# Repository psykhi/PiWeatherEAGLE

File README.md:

PiWeatherEAGLE
==============

This repository contains EAGLE boards/schematics/gerber files for the PiWeather weather station project.
To learn more, see http://theboredengineers.com.

main_indoor_sensor is an indoor board that can monitor temperature, humidity and pressure.
It is described here : http://theboredengineers.com/2014/05/piweather-part-4-first-pcbs/

rpi_shield is Raspberry Pi shield hosting a nRF24L01+ RF transimtter. 

If you are interested in this project, please visit http://theboredengineers.com, let a comment
or send an email to alex@theboredengineers.com

:)

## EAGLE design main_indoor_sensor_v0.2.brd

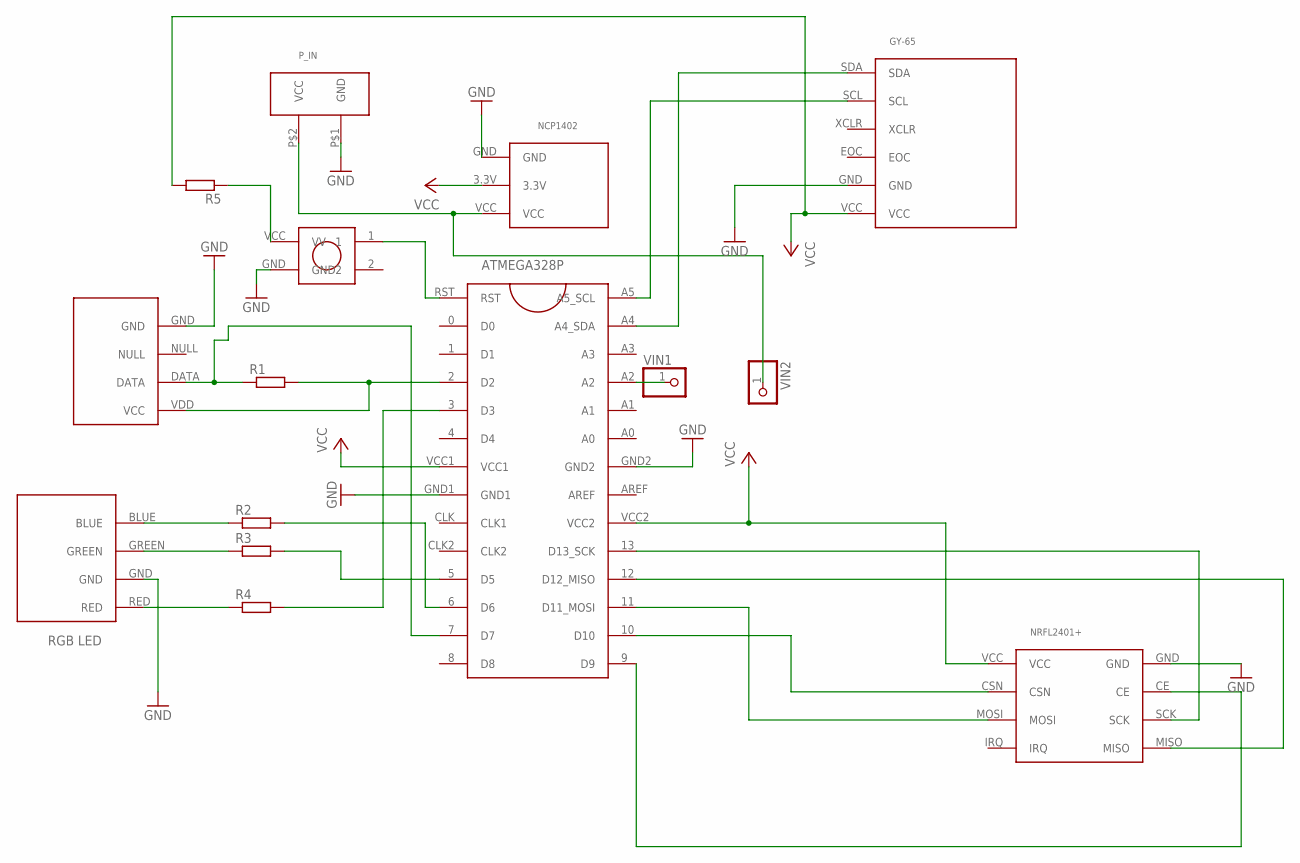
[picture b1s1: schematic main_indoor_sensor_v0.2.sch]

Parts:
GY-65: GY-65; GY_65
NCP1402: NCP1402SPARKFUN; NCP1402
NRFL2401+: NRFL24L01_8P; NRF24L01_10P
P_IN: 2PINCONNECTORSIMPLE; 2PINCONNECTOR
R1, R2, R3, R4, R5: R0204/7; 0204/7
U$1: ATMEGA328PARDUINO; ATMEGA328P
U$2: KRS_0612_OK; KRS0612_RIGHT
U$3: DHT22WHITE; DHT22
U$6: RGB_LED5MM; RGB_LED
VIN1, VIN2: PINHD-1X1; 1X01

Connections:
GND: GY-65.GND, NCP1402.GND, NRFL2401+.GND, P_IN.P$1 (GND), U$1.GND1, U$1.GND2, U$2.GND, U$3.GND, U$6.GND
unnamed: GY-65.SDA, U$1.A4 (A4_SDA)
unnamed: GY-65.SCL, U$1.A5 (A5_SCL)
unnamed: NRFL2401+.SCK, U$1.13 (D13_SCK)
unnamed: NRFL2401+.MISO, U$1.12 (D12_MISO)
unnamed: NRFL2401+.MOSI, U$1.11 (D11_MOSI)
unnamed: R1.2, U$1.2 (D2), U$3.VDD (VCC)
unnamed: R1.1, U$1.7 (D7), U$3.DATA
unnamed: R4.2, U$1.3 (D3)
unnamed: R2.1, U$6.BLUE
unnamed: R3.1, U$6.GREEN
unnamed: R2.2, U$1.6 (D6)
unnamed: R3.2, U$1.5 (D5)
unnamed: R4.1, U$6.RED
unnamed: NRFL2401+.CSN, U$1.10 (D10)
unnamed: NRFL2401+.CE, U$1.9 (D9)
unnamed: U$1.RST, U$2.1
unnamed: NCP1402.VCC, P_IN.P$2 (VCC), VIN2.1
unnamed: R5.1, U$2.VCC (VV)
unnamed: U$1.A2, VIN1.1
VCC: GY-65.VCC, NCP1402.3.3V, NRFL2401+.VCC, R5.2, U$1.VCC1, U$1.VCC2

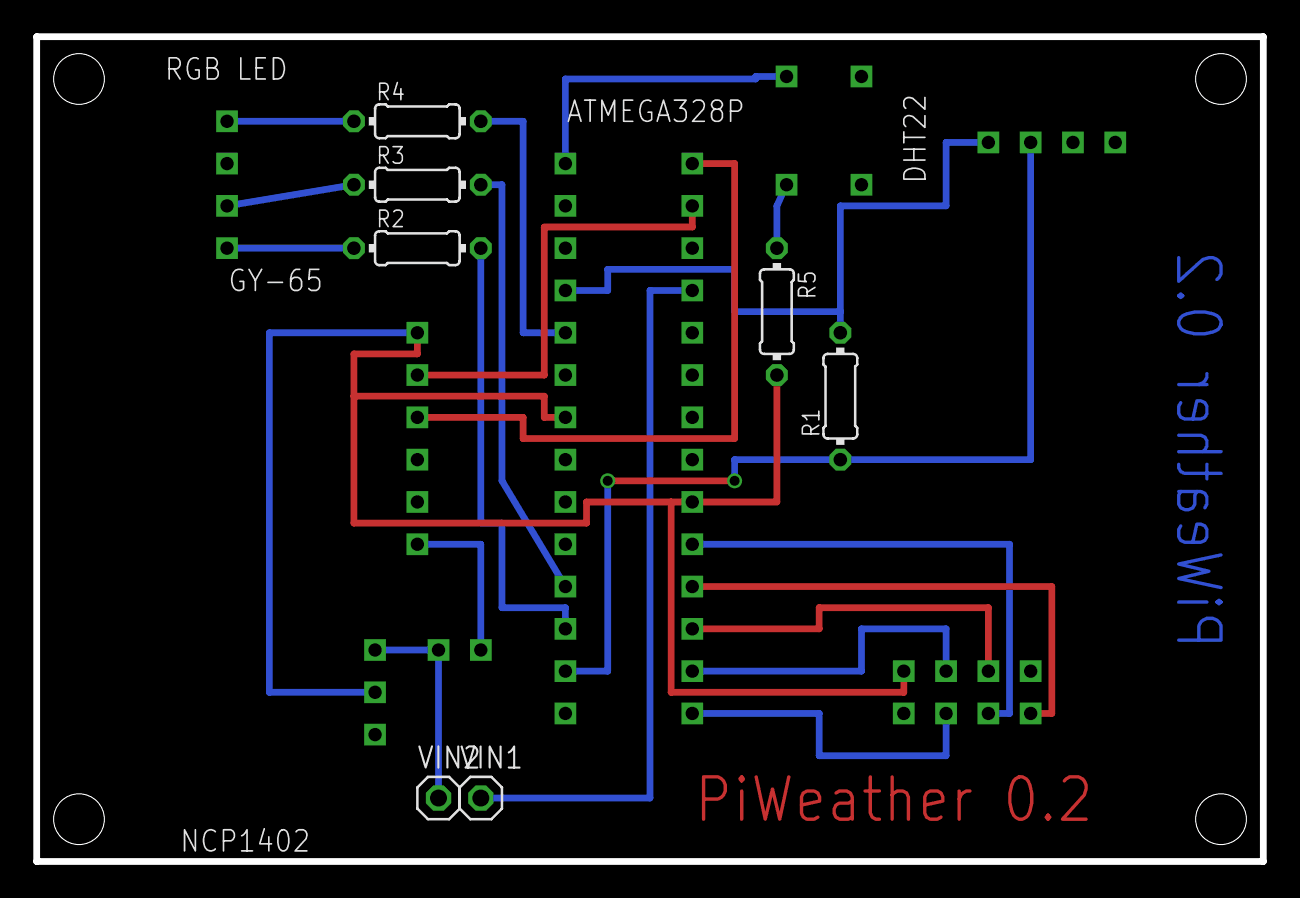
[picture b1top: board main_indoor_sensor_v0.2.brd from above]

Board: 2 copper layers, 73.7 x 49.5 mm, 15 parts (0 on the bottom side), 21 nets.

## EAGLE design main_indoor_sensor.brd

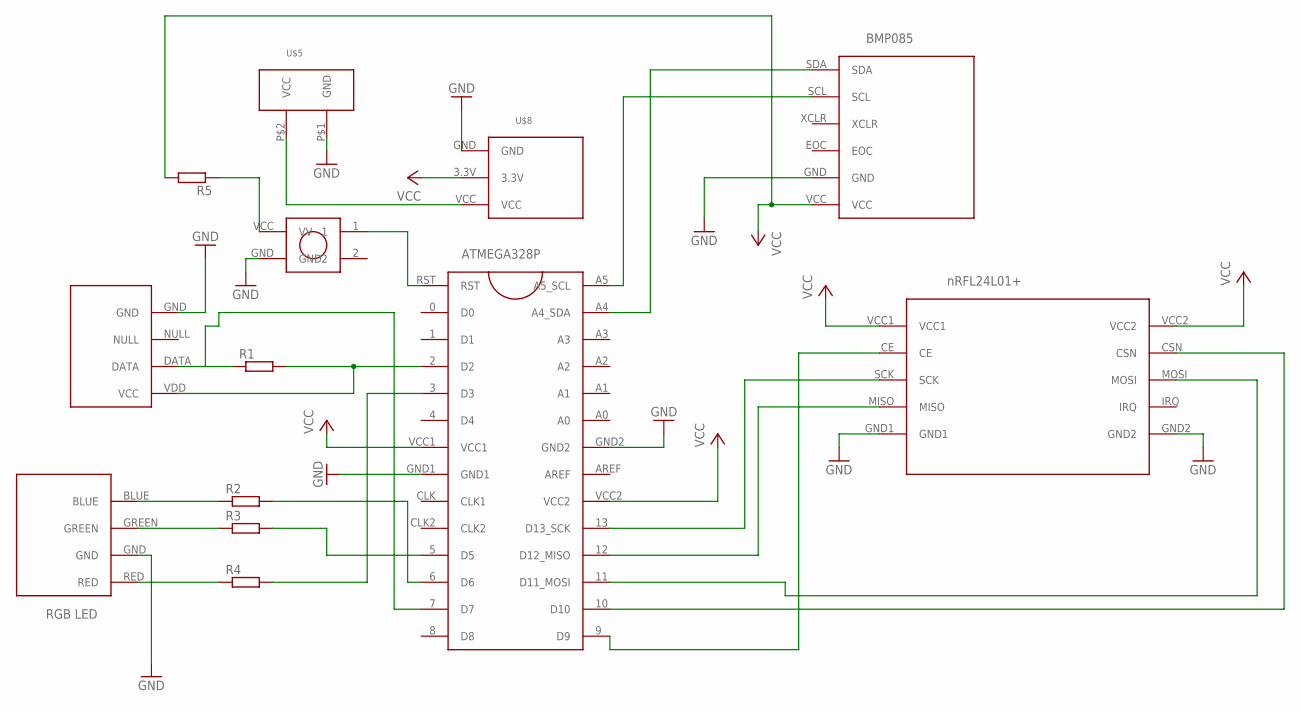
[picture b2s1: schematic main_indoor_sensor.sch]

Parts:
R1, R2, R3, R4, R5: R0204/7; 0204/7
U$1: ATMEGA328PARDUINO; ATMEGA328P
U$2: BMP085SPARKFUN; BMP085
U$3: DHT22WHITE; DHT22
U$4: NRF24L0110PINS; NRF24L01
U$5: 2PINCONNECTORSIMPLE; 2PINCONNECTOR
U$6: RGB_LED5MM; RGB_LED
U$7: KRS0612PUSH; KRS0612
U$8: NCP1402SPARKFUN; NCP1402

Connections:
GND: U$1.GND1, U$1.GND2, U$2.GND, U$3.GND, U$4.GND1, U$4.GND2, U$5.P$1 (GND), U$6.GND, U$7.GND, U$8.GND
unnamed: U$1.A4 (A4_SDA), U$2.SDA
unnamed: U$1.A5 (A5_SCL), U$2.SCL
unnamed: U$1.13 (D13_SCK), U$4.SCK
unnamed: U$1.12 (D12_MISO), U$4.MISO
unnamed: U$1.11 (D11_MOSI), U$4.MOSI
unnamed: R1.2, U$1.2 (D2), U$3.VDD (VCC)
unnamed: R1.1, U$1.7 (D7), U$3.DATA
unnamed: R4.2, U$1.3 (D3)
unnamed: R2.1, U$6.BLUE
unnamed: R3.1, U$6.GREEN
unnamed: R2.2, U$1.6 (D6)
unnamed: R3.2, U$1.5 (D5)
unnamed: R4.1, U$6.RED
unnamed: U$1.10 (D10), U$4.CSN
unnamed: U$1.9 (D9), U$4.CE
unnamed: U$1.RST, U$7.1
unnamed: U$5.P$2 (VCC), U$8.VCC
unnamed: R5.1, U$7.VCC (VV)
RASTNEST: R5.2, U$1.VCC1, U$1.VCC2, U$2.VCC, U$4.VCC1, U$4.VCC2, U$8.3.3V

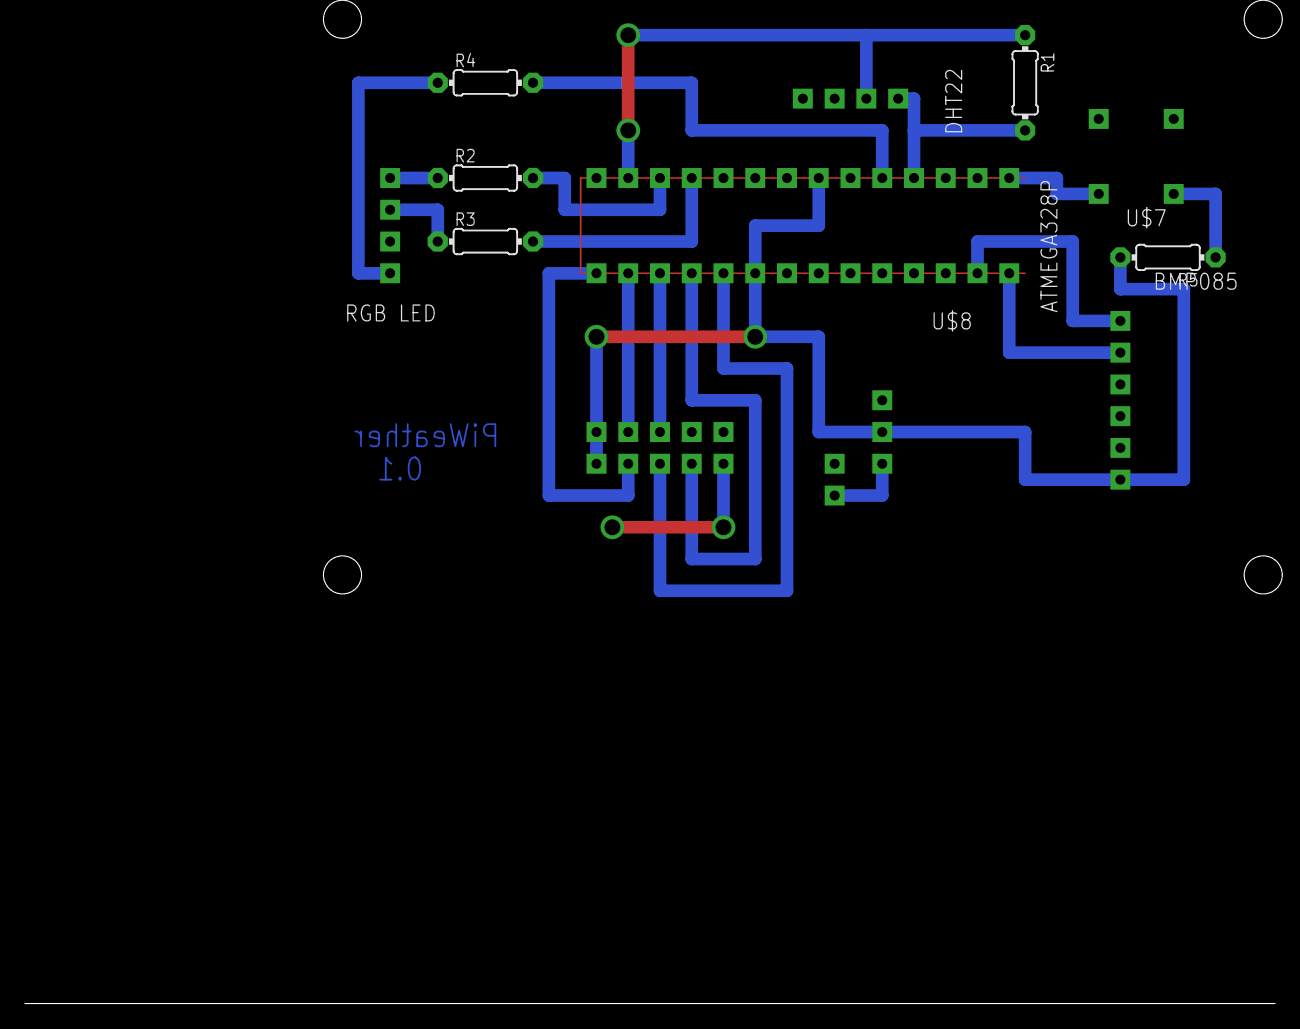
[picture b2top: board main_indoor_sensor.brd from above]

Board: 2 copper layers, 13 parts (0 on the bottom side), 20 nets.

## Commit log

2014-02-14 fusion des deux repos eagle
2014-02-15 Version 0.1 avec prototype créé
2014-04-05 Added Seeedstudio design rules New version (0.2) of the board...ON VERRA
2014-04-05 Added Gerber file...
2014-04-05 Added zip file sent to seeedstudio for v0.2
2014-04-09 Nouvelle version avec la board outline :o
2014-09-10 Added Raspberry Pi GPIO header to the library
2014-09-10 Added RPI shield
